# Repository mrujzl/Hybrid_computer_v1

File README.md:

# Hybrid_computer_v1
Hybrid computer for study of nonlinear dynamic systems. It was developed at Department of Radio Electronics, Brno University of Technology within the grant Development of analog computer with hybrid analog-digital components for accurate modeling of chaotic systems. This grant is realised within the project Quality Internal Grants of BUT (KInG BUT), Reg. No. CZ.02.2.69 / 0.0 / 0.0 / 19_073 / 0016948, which is financed from the OP RDE.

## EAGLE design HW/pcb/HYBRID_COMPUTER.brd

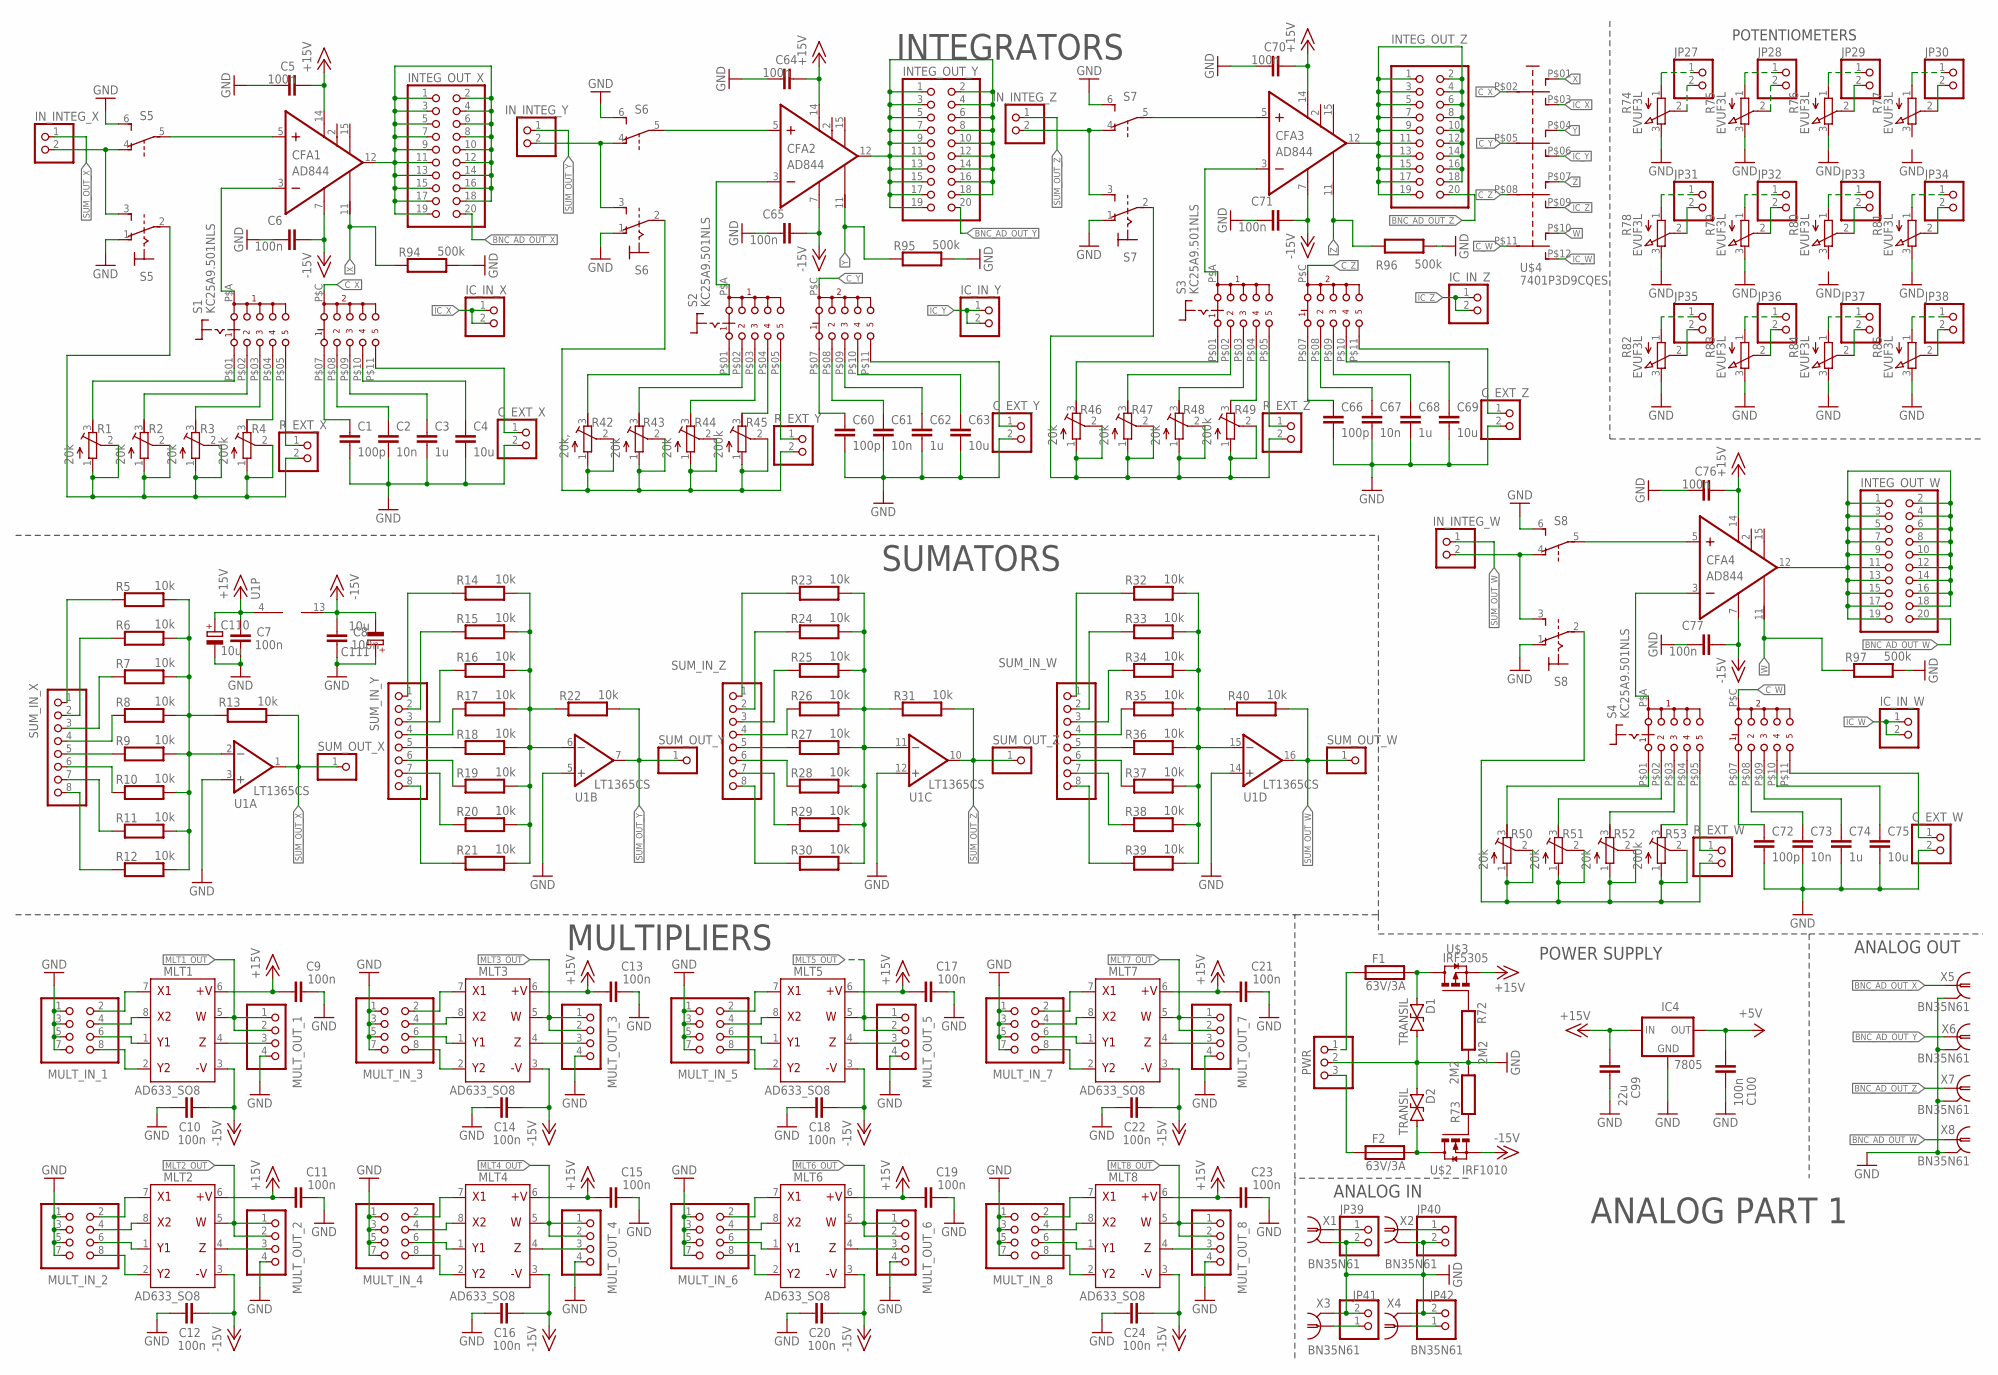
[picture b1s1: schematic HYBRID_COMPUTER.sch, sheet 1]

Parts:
C1, C60, C66, C72: 100p; C_1206
C2, C61, C67, C73: 10n; C_1206
C3, C62, C68, C74: 1u; C_1206
C4, C63, C69, C75: 10u; C_1206
C5, C6, C7, C8, C9, C10, C11, C12, C13, C14, C15, C16, C17, C18, C19, C20, C21, C22, C23, C24, C64, C65, C70, C71, C76, C77, C100: 100n; C_1206
C99: 22u; C_1206
C110, C111: 10u; E2,5-5
CFA1, CFA2, CFA3, CFA4: AD844; SOIC16R
C_EXT_W: PINHD-1X2; 1X02
C_EXT_X: PINHD-1X2; 1X02
C_EXT_Y: PINHD-1X2; 1X02
C_EXT_Z: PINHD-1X2; 1X02
D1, D2: TRANSIL; DO15-12
F1, F2: 63V/3A; FUSE_1206
IC4: 7805; 78MXXS
IC_IN_W: PINHD-1X2; 1X02
IC_IN_X: PINHD-1X2; 1X02
IC_IN_Y: PINHD-1X2; 1X02
IC_IN_Z: PINHD-1X2; 1X02
INTEG_OUT_W: PINHD-2X10; 2X10
INTEG_OUT_X: PINHD-2X10; 2X10
INTEG_OUT_Y: PINHD-2X10; 2X10
INTEG_OUT_Z: PINHD-2X10; 2X10
IN_INTEG_W: PINHD-1X2; 1X02
IN_INTEG_X: PINHD-1X2; 1X02
IN_INTEG_Y: PINHD-1X2; 1X02
IN_INTEG_Z: PINHD-1X2; 1X02
JP27, JP28, JP29, JP30, JP31, JP32, JP33, JP34, JP35, JP36, JP37, JP38, JP39, JP40, JP41, JP42: PINHD-1X2; 1X02
MLT1, MLT2, MLT3, MLT4, MLT5, MLT6, MLT7, MLT8: AD633_SO8; SO8
MULT_IN_1, MULT_IN_2, MULT_IN_3, MULT_IN_4, MULT_IN_5, MULT_IN_6, MULT_IN_7, MULT_IN_8: PINHD-2X4; 2X04
MULT_OUT_1, MULT_OUT_2, MULT_OUT_3, MULT_OUT_4, MULT_OUT_5, MULT_OUT_6, MULT_OUT_7, MULT_OUT_8: PINHD-1X4; 1X04
PWR: PINHD-1X3; 1X03
R1, R2, R3, R43, R44, R46, R47, R48, R50, R51, R52: 20k; RTRIM64W
R4, R45, R49, R53: 200k; RTRIM64W
R5, R6, R7, R8, R9, R10, R11, R12, R13, R14, R15, R16, R17, R18, R19, R20, R21, R22, R23, R24, R25, R26, R27, R28, R29, R30, R31, R32, R33, R34, R35, R36, R37, R38, R39, R40: 10k; R_1206
R42: 20k,; RTRIM64W
R72, R73: 2M2; R_1206
R74, R75, R76, R77, R78, R79, R80, R81, R82, R83, R84, R85: EVUF3L; EVUFXL
R94, R95, R96, R97: 500k; R_1206
R_EXT_W: PINHD-1X2; 1X02
R_EXT_X: PINHD-1X2; 1X02
R_EXT_Y: PINHD-1X2; 1X02
R_EXT_Z: PINHD-1X2; 1X02
S1, S2, S3, S4: KC25A9.501NLS
S5, S6, S7, S8: 320-938
SUM_IN_W: PINHD-1X8; 1X08
SUM_IN_X: PINHD-1X8; 1X08
SUM_IN_Y: PINHD-1X8; 1X08
SUM_IN_Z: PINHD-1X8; 1X08
SUM_OUT_W: PINHD-1X1; 1X01
SUM_OUT_X: PINHD-1X1; 1X01
SUM_OUT_Y: PINHD-1X1; 1X01
SUM_OUT_Z: PINHD-1X1; 1X01
U1: LT1365CS; SO16
U$2: IRF1010; TO220BV
U$3: IRF5305; TO220BV
U$4: 7401P3D9CQES
X1, X2, X3, X4, X5, X6, X7, X8: BN35N61; B35N61

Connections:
+5V: C100.1, IC4.OUT; also elsewhere on the board
+15V: C5.1, C7.1, C9.1, C11.1, C13.1, C15.1, C17.1, C19.1, C21.1, C23.1, C64.1, C70.1, C76.1, C99.1, C110.+, CFA1.14 (7), CFA2.14 (7), CFA3.14 (7), CFA4.14 (7), IC4.IN, MLT1.6 (8), MLT2.6 (8), MLT3.6 (8), MLT4.6 (8), MLT5.6 (8), MLT6.6 (8), MLT7.6 (8), MLT8.6 (8), U1.4 (V+), U$3.S; also elsewhere on the board
-15V: C6.1, C8.1, C10.1, C12.1, C14.1, C16.1, C18.1, C20.1, C22.1, C24.1, C65.1, C71.1, C77.1, C111.-, CFA1.7 (4), CFA2.7 (4), CFA3.7 (4), CFA4.7 (4), MLT1.3 (5), MLT2.3 (5), MLT3.3 (5), MLT4.3 (5), MLT5.3 (5), MLT6.3 (5), MLT7.3 (5), MLT8.3 (5), U1.13 (V-), U$2.S; also elsewhere on the board
BNC_AD_OUT_W: INTEG_OUT_W.20, X8.1; also elsewhere on the board
BNC_AD_OUT_X: INTEG_OUT_X.20, X5.1; also elsewhere on the board
BNC_AD_OUT_Y: INTEG_OUT_Y.20, X6.1; also elsewhere on the board
BNC_AD_OUT_Z: INTEG_OUT_Z.20, X7.1; also elsewhere on the board
C_W: S4.P$C (C), U$4.P$11 (11)
C_X: S1.P$C (C), U$4.P$02 (2)
C_Y: S2.P$C (C), U$4.P$05 (5)
C_Z: S3.P$C (C), U$4.P$08 (8)
GND: C1.2, C2.2, C3.2, C4.2, C5.2, C6.2, C7.2, C8.2, C9.2, C10.2, C11.2, C12.2, C13.2, C14.2, C15.2, C16.2, C17.2, C18.2, C19.2, C20.2, C21.2, C22.2, C23.2, C24.2, C60.2, C61.2, C62.2, C63.2, C64.2, C65.2, C66.2, C67.2, C68.2, C69.2, C70.2, C71.2, C72.2, C73.2, C74.2, C75.2, C76.2, C77.2, C99.2, C100.2, C110.-, C111.+, C_EXT_W.2, C_EXT_X.2, C_EXT_Y.2, C_EXT_Z.2, D1.C, D2.A, IC4.GND, JP39.2, JP40.2, JP41.2, JP42.2, MULT_IN_1.1, MULT_IN_1.3, MULT_IN_1.5, MULT_IN_1.7, MULT_IN_2.1, MULT_IN_2.3, MULT_IN_2.5, MULT_IN_2.7, MULT_IN_3.1, MULT_IN_3.3, MULT_IN_3.5, MULT_IN_3.7, MULT_IN_4.1, MULT_IN_4.3, MULT_IN_4.5, MULT_IN_4.7, MULT_IN_5.1, MULT_IN_5.3, MULT_IN_5.5, MULT_IN_5.7, MULT_IN_6.1, MULT_IN_6.3, MULT_IN_6.5, MULT_IN_6.7, MULT_IN_7.1, MULT_IN_7.3, MULT_IN_7.5, MULT_IN_7.7, MULT_IN_8.1, MULT_IN_8.3, MULT_IN_8.5, MULT_IN_8.7, MULT_OUT_1.4, MULT_OUT_2.4, MULT_OUT_3.4, MULT_OUT_4.4, MULT_OUT_5.4, MULT_OUT_6.4, MULT_OUT_7.4, MULT_OUT_8.4, PWR.2, R72.2, R73.2, R74.3 (E), R75.3 (E), R76.3 (E), R78.3 (E), R79.3 (E), R81.3 (E), R82.3 (E), R83.3 (E), R84.3 (E), R85.3 (E), R94.2, R95.2, R96.2, R97.2, S5.1 (O), S5.6 (S), S6.1 (O), S6.6 (S), S7.1 (O), S7.6 (S), S8.1 (O), S8.6 (S), U1.3 (+IN), U1.5 (+IN), U1.12 (+IN), U1.14 (+IN), X1.2, X1.3 (2), X1.4 (2), X1.5 (2), X2.2, X2.3 (2), X2.4 (2), X2.5 (2), X3.2, X3.3 (2), X3.4 (2), X3.5 (2), X4.2, X4.3 (2), X4.4 (2), X4.5 (2), X5.2, X5.3 (2), X5.4 (2), X5.5 (2), X6.2, X6.3 (2), X6.4 (2), X6.5 (2), X7.2, X7.3 (2), X7.4 (2), X7.5 (2), X8.2, X8.3 (2), X8.4 (2), X8.5 (2); also elsewhere on the board
IC_W: IC_IN_W.1, IC_IN_W.2, U$4.P$12 (12)
IC_X: IC_IN_X.1, IC_IN_X.2, U$4.P$03 (3)
IC_Y: IC_IN_Y.1, IC_IN_Y.2, U$4.P$06 (6)
IC_Z: IC_IN_Z.1, IC_IN_Z.2, U$4.P$09 (9)
INTEG_OUT_W: CFA4.12 (6), INTEG_OUT_W.1, INTEG_OUT_W.2, INTEG_OUT_W.3, INTEG_OUT_W.4, INTEG_OUT_W.5, INTEG_OUT_W.6, INTEG_OUT_W.7, INTEG_OUT_W.8, INTEG_OUT_W.9, INTEG_OUT_W.10, INTEG_OUT_W.11, INTEG_OUT_W.12, INTEG_OUT_W.13, INTEG_OUT_W.14, INTEG_OUT_W.15, INTEG_OUT_W.16, INTEG_OUT_W.17, INTEG_OUT_W.18, INTEG_OUT_W.19
INTEG_OUT_Y: CFA2.12 (6), INTEG_OUT_Y.1, INTEG_OUT_Y.2, INTEG_OUT_Y.3, INTEG_OUT_Y.4, INTEG_OUT_Y.5, INTEG_OUT_Y.6, INTEG_OUT_Y.7, INTEG_OUT_Y.8, INTEG_OUT_Y.9, INTEG_OUT_Y.10, INTEG_OUT_Y.11, INTEG_OUT_Y.12, INTEG_OUT_Y.13, INTEG_OUT_Y.14, INTEG_OUT_Y.15, INTEG_OUT_Y.16, INTEG_OUT_Y.17, INTEG_OUT_Y.18, INTEG_OUT_Y.19
INTEG_OUT_Z: CFA3.12 (6), INTEG_OUT_Z.1, INTEG_OUT_Z.2, INTEG_OUT_Z.3, INTEG_OUT_Z.4, INTEG_OUT_Z.5, INTEG_OUT_Z.6, INTEG_OUT_Z.7, INTEG_OUT_Z.8, INTEG_OUT_Z.9, INTEG_OUT_Z.10, INTEG_OUT_Z.11, INTEG_OUT_Z.12, INTEG_OUT_Z.13, INTEG_OUT_Z.14, INTEG_OUT_Z.15, INTEG_OUT_Z.16, INTEG_OUT_Z.17, INTEG_OUT_Z.18, INTEG_OUT_Z.19
MLT1_OUT: MLT1.5 (7), MULT_OUT_1.1, MULT_OUT_1.2
MLT2_OUT: MLT2.5 (7), MULT_OUT_2.1, MULT_OUT_2.2
MLT3_OUT: MLT3.5 (7), MULT_OUT_3.1, MULT_OUT_3.2
MLT4_OUT: MLT4.5 (7), MULT_OUT_4.1, MULT_OUT_4.2
MLT5_OUT: MLT5.5 (7), MULT_OUT_5.1, MULT_OUT_5.2
MLT6_OUT: MLT6.5 (7), MULT_OUT_6.1, MULT_OUT_6.2
MLT7_OUT: MLT7.5 (7), MULT_OUT_7.1, MULT_OUT_7.2
MLT8_OUT: MLT8.5 (7), MULT_OUT_8.1, MULT_OUT_8.2
unnamed: R1.1 (A), R1.2 (S), R2.1 (A), R2.2 (S), R3.1 (A), R3.2 (S), R4.1 (A), R4.2 (S), R_EXT_X.2, S5.2
unnamed: CFA1.5 (3), S5.5
unnamed: CFA1.3 (2), S1.P$A (A)
unnamed: IN_INTEG_X.2, S5.3 (S), S5.4 (O)
unnamed: R4.3 (E), S1.P$04 (4)
unnamed: R1.3 (E), S1.P$01 (1)
unnamed: R2.3 (E), S1.P$02 (2)
unnamed: R3.3 (E), S1.P$03 (3)
unnamed: C1.1, S1.P$07 (7)
unnamed: R5.2, R6.2, R7.2, R8.2, R9.2, R10.2, R11.2, R12.2, R13.1, U1.2 (-IN)
unnamed: C4.1, S1.P$10 (10)
unnamed: C3.1, S1.P$09 (9)
unnamed: C2.1, S1.P$08 (8)
unnamed: R_EXT_X.1, S1.P$05 (5)
unnamed: R9.1, SUM_IN_X.5
unnamed: C_EXT_X.1, S1.P$11 (11)
unnamed: R10.1, SUM_IN_X.6
unnamed: R11.1, SUM_IN_X.7
unnamed: R12.1, SUM_IN_X.8
unnamed: R8.1, SUM_IN_X.4
unnamed: R7.1, SUM_IN_X.3
unnamed: R6.1, SUM_IN_X.2
unnamed: R5.1, SUM_IN_X.1
unnamed: R14.2, R15.2, R16.2, R17.2, R18.2, R19.2, R20.2, R21.2, R22.1, U1.6 (-IN)
unnamed: JP29.2, R76.2 (S)
unnamed: R18.1, SUM_IN_Y.5
unnamed: R19.1, SUM_IN_Y.6
unnamed: R20.1, SUM_IN_Y.7
unnamed: R21.1, SUM_IN_Y.8
unnamed: R17.1, SUM_IN_Y.4
unnamed: R16.1, SUM_IN_Y.3
unnamed: R15.1, SUM_IN_Y.2
unnamed: R14.1, SUM_IN_Y.1
unnamed: R23.2, R24.2, R25.2, R26.2, R27.2, R28.2, R29.2, R30.2, R31.1, U1.11 (-IN)
unnamed: MLT1.7 (1), MULT_IN_1.2
unnamed: R27.1, SUM_IN_Z.5
unnamed: R28.1, SUM_IN_Z.6
unnamed: R29.1, SUM_IN_Z.7
unnamed: R30.1, SUM_IN_Z.8
unnamed: R26.1, SUM_IN_Z.4
unnamed: R25.1, SUM_IN_Z.3
unnamed: R24.1, SUM_IN_Z.2
unnamed: R23.1, SUM_IN_Z.1
unnamed: R32.2, R33.2, R34.2, R35.2, R36.2, R37.2, R38.2, R39.2, R40.1, U1.15 (-IN)
unnamed: R36.1, SUM_IN_W.5
unnamed: R37.1, SUM_IN_W.6
unnamed: R38.1, SUM_IN_W.7
unnamed: R39.1, SUM_IN_W.8
unnamed: R35.1, SUM_IN_W.4
unnamed: R34.1, SUM_IN_W.3
unnamed: R33.1, SUM_IN_W.2
unnamed: R32.1, SUM_IN_W.1
unnamed: MLT1.4 (6), MULT_OUT_1.3
unnamed: MLT1.8 (2), MULT_IN_1.4
unnamed: MLT1.1 (3), MULT_IN_1.6
unnamed: MLT1.2 (4), MULT_IN_1.8
unnamed: MLT2.4 (6), MULT_OUT_2.3
unnamed: MLT2.7 (1), MULT_IN_2.2
unnamed: MLT2.8 (2), MULT_IN_2.4
unnamed: MLT2.1 (3), MULT_IN_2.6
unnamed: MLT2.2 (4), MULT_IN_2.8
unnamed: MLT3.4 (6), MULT_OUT_3.3
unnamed: MLT3.7 (1), MULT_IN_3.2
unnamed: MLT3.8 (2), MULT_IN_3.4
unnamed: MLT3.1 (3), MULT_IN_3.6
unnamed: MLT3.2 (4), MULT_IN_3.8
unnamed: R46.1 (A), R46.2 (S), R47.1 (A), R47.2 (S), R48.1 (A), R48.2 (S), R49.1 (A), R49.2 (S), R_EXT_Z.2, S7.2
unnamed: MLT4.4 (6), MULT_OUT_4.3
unnamed: MLT4.7 (1), MULT_IN_4.2
unnamed: MLT4.8 (2), MULT_IN_4.4
unnamed: MLT4.1 (3), MULT_IN_4.6
unnamed: MLT4.2 (4), MULT_IN_4.8
unnamed: MLT5.4 (6), MULT_OUT_5.3
unnamed: MLT5.7 (1), MULT_IN_5.2
unnamed: MLT5.8 (2), MULT_IN_5.4
unnamed: MLT5.1 (3), MULT_IN_5.6
unnamed: MLT5.2 (4), MULT_IN_5.8
unnamed: MLT6.4 (6), MULT_OUT_6.3
unnamed: MLT6.7 (1), MULT_IN_6.2
unnamed: MLT6.8 (2), MULT_IN_6.4
unnamed: MLT6.1 (3), MULT_IN_6.6
unnamed: MLT6.2 (4), MULT_IN_6.8
unnamed: MLT7.4 (6), MULT_OUT_7.3
unnamed: MLT7.7 (1), MULT_IN_7.2
unnamed: MLT7.8 (2), MULT_IN_7.4
unnamed: MLT7.1 (3), MULT_IN_7.6
unnamed: MLT7.2 (4), MULT_IN_7.8
unnamed: MLT8.4 (6), MULT_OUT_8.3
unnamed: MLT8.7 (1), MULT_IN_8.2
unnamed: MLT8.8 (2), MULT_IN_8.4
unnamed: MLT8.1 (3), MULT_IN_8.6
unnamed: MLT8.2 (4), MULT_IN_8.8
unnamed: JP27.1, R74.1 (A)
unnamed: JP27.2, R74.2 (S)
unnamed: JP28.2, R75.2 (S)
unnamed: JP28.1, R75.1 (A)
unnamed: JP29.1, R76.1 (A)
unnamed: JP30.1, R77.1 (A)
unnamed: JP30.2, R77.2 (S)
unnamed: JP34.1, R81.1 (A)
unnamed: JP34.2, R81.2 (S)
unnamed: JP33.2, R80.2 (S)
unnamed: JP33.1, R80.1 (A)
unnamed: JP32.1, R79.1 (A)
unnamed: JP32.2, R79.2 (S)
unnamed: JP31.1, R78.1 (A)
unnamed: JP31.2, R78.2 (S)
unnamed: JP35.1, R82.1 (A)
unnamed: JP35.2, R82.2 (S)
unnamed: JP36.1, R83.1 (A)
unnamed: JP36.2, R83.2 (S)
unnamed: JP37.1, R84.1 (A)
unnamed: JP37.2, R84.2 (S)
unnamed: JP38.1, R85.1 (A)
unnamed: JP38.2, R85.2 (S)
unnamed: D1.A, F1.2, U$3.D
unnamed: R42.1 (A), R42.2 (S), R43.1 (A), R43.2 (S), R44.1 (A), R44.2 (S), R45.1 (A), R45.2 (S), R_EXT_Y.2, S6.2
unnamed: CFA2.5 (3), S6.5
unnamed: CFA2.3 (2), S2.P$A (A)
unnamed: IN_INTEG_Y.2, S6.3 (S), S6.4 (O)
unnamed: R42.3 (E), S2.P$01 (1)
unnamed: R43.3 (E), S2.P$02 (2)
unnamed: R44.3 (E), S2.P$03 (3)
unnamed: C63.1, S2.P$10 (10)
unnamed: C62.1, S2.P$09 (9)
unnamed: C61.1, S2.P$08 (8)
unnamed: CFA1.12 (6), INTEG_OUT_X.1, INTEG_OUT_X.2, INTEG_OUT_X.3, INTEG_OUT_X.4, INTEG_OUT_X.5, INTEG_OUT_X.6, INTEG_OUT_X.7, INTEG_OUT_X.8, INTEG_OUT_X.9, INTEG_OUT_X.10, INTEG_OUT_X.11, INTEG_OUT_X.12, INTEG_OUT_X.13, INTEG_OUT_X.14, INTEG_OUT_X.15, INTEG_OUT_X.16, INTEG_OUT_X.17, INTEG_OUT_X.18, INTEG_OUT_X.19
unnamed: R45.3 (E), S2.P$04 (4)
unnamed: C60.1, S2.P$07 (7)
unnamed: R_EXT_Y.1, S2.P$05 (5)
unnamed: C_EXT_Y.1, S2.P$11 (11)
unnamed: CFA3.5 (3), S7.5
unnamed: CFA3.3 (2), S3.P$A (A)
unnamed: IN_INTEG_Z.2, S7.3 (S), S7.4 (O)
unnamed: R46.3 (E), S3.P$01 (1)
unnamed: R47.3 (E), S3.P$02 (2)
unnamed: R48.3 (E), S3.P$03 (3)
unnamed: C69.1, S3.P$10 (10)
unnamed: C68.1, S3.P$09 (9)
unnamed: C67.1, S3.P$08 (8)
unnamed: R49.3 (E), S3.P$04 (4)
unnamed: C66.1, S3.P$07 (7)
unnamed: R_EXT_Z.1, S3.P$05 (5)
unnamed: C_EXT_Z.1, S3.P$11 (11)
unnamed: R50.1 (A), R50.2 (S), R51.1 (A), R51.2 (S), R52.1 (A), R52.2 (S), R53.1 (A), R53.2 (S), R_EXT_W.2, S8.2
unnamed: CFA4.5 (3), S8.5
unnamed: CFA4.3 (2), S4.P$A (A)
unnamed: IN_INTEG_W.2, S8.3 (S), S8.4 (O)
unnamed: R50.3 (E), S4.P$01 (1)
unnamed: R51.3 (E), S4.P$02 (2)
unnamed: R52.3 (E), S4.P$03 (3)
unnamed: C75.1, S4.P$10 (10)
unnamed: C74.1, S4.P$09 (9)
unnamed: C73.1, S4.P$08 (8)
unnamed: R53.3 (E), S4.P$04 (4)
unnamed: C72.1, S4.P$07 (7)
unnamed: R_EXT_W.1, S4.P$05 (5)
unnamed: C_EXT_W.1, S4.P$11 (11)
unnamed: F2.1, PWR.3
unnamed: F1.1, PWR.1
unnamed: JP39.1, X1.1
unnamed: JP40.1, X2.1
unnamed: JP41.1, X3.1
unnamed: JP42.1, X4.1
unnamed: D2.C, F2.2, U$2.D
unnamed: R72.1, U$3.G
unnamed: R73.1, U$2.G
SUM_OUT_W: IN_INTEG_W.1, R40.2, SUM_OUT_W.1, U1.16 (OUT)
SUM_OUT_X: IN_INTEG_X.1, R13.2, SUM_OUT_X.1, U1.1 (OUT)
SUM_OUT_Y: IN_INTEG_Y.1, R22.2, SUM_OUT_Y.1, U1.7 (OUT)
SUM_OUT_Z: IN_INTEG_Z.1, R31.2, SUM_OUT_Z.1, U1.10 (OUT)
W: CFA4.11 (5), R97.1, U$4.P$10 (10)
X: CFA1.11 (5), R94.1, U$4.P$01 (1)
Y: CFA2.11 (5), R95.1, U$4.P$04 (4)
Z: CFA3.11 (5), R96.1, U$4.P$07 (7)

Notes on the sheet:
ANALOG PART 1
INTEGRATORS
ANALOG OUT
SUMATORS
POWER SUPPLY
MULTIPLIERS
POTENTIOMETERS
ANALOG IN

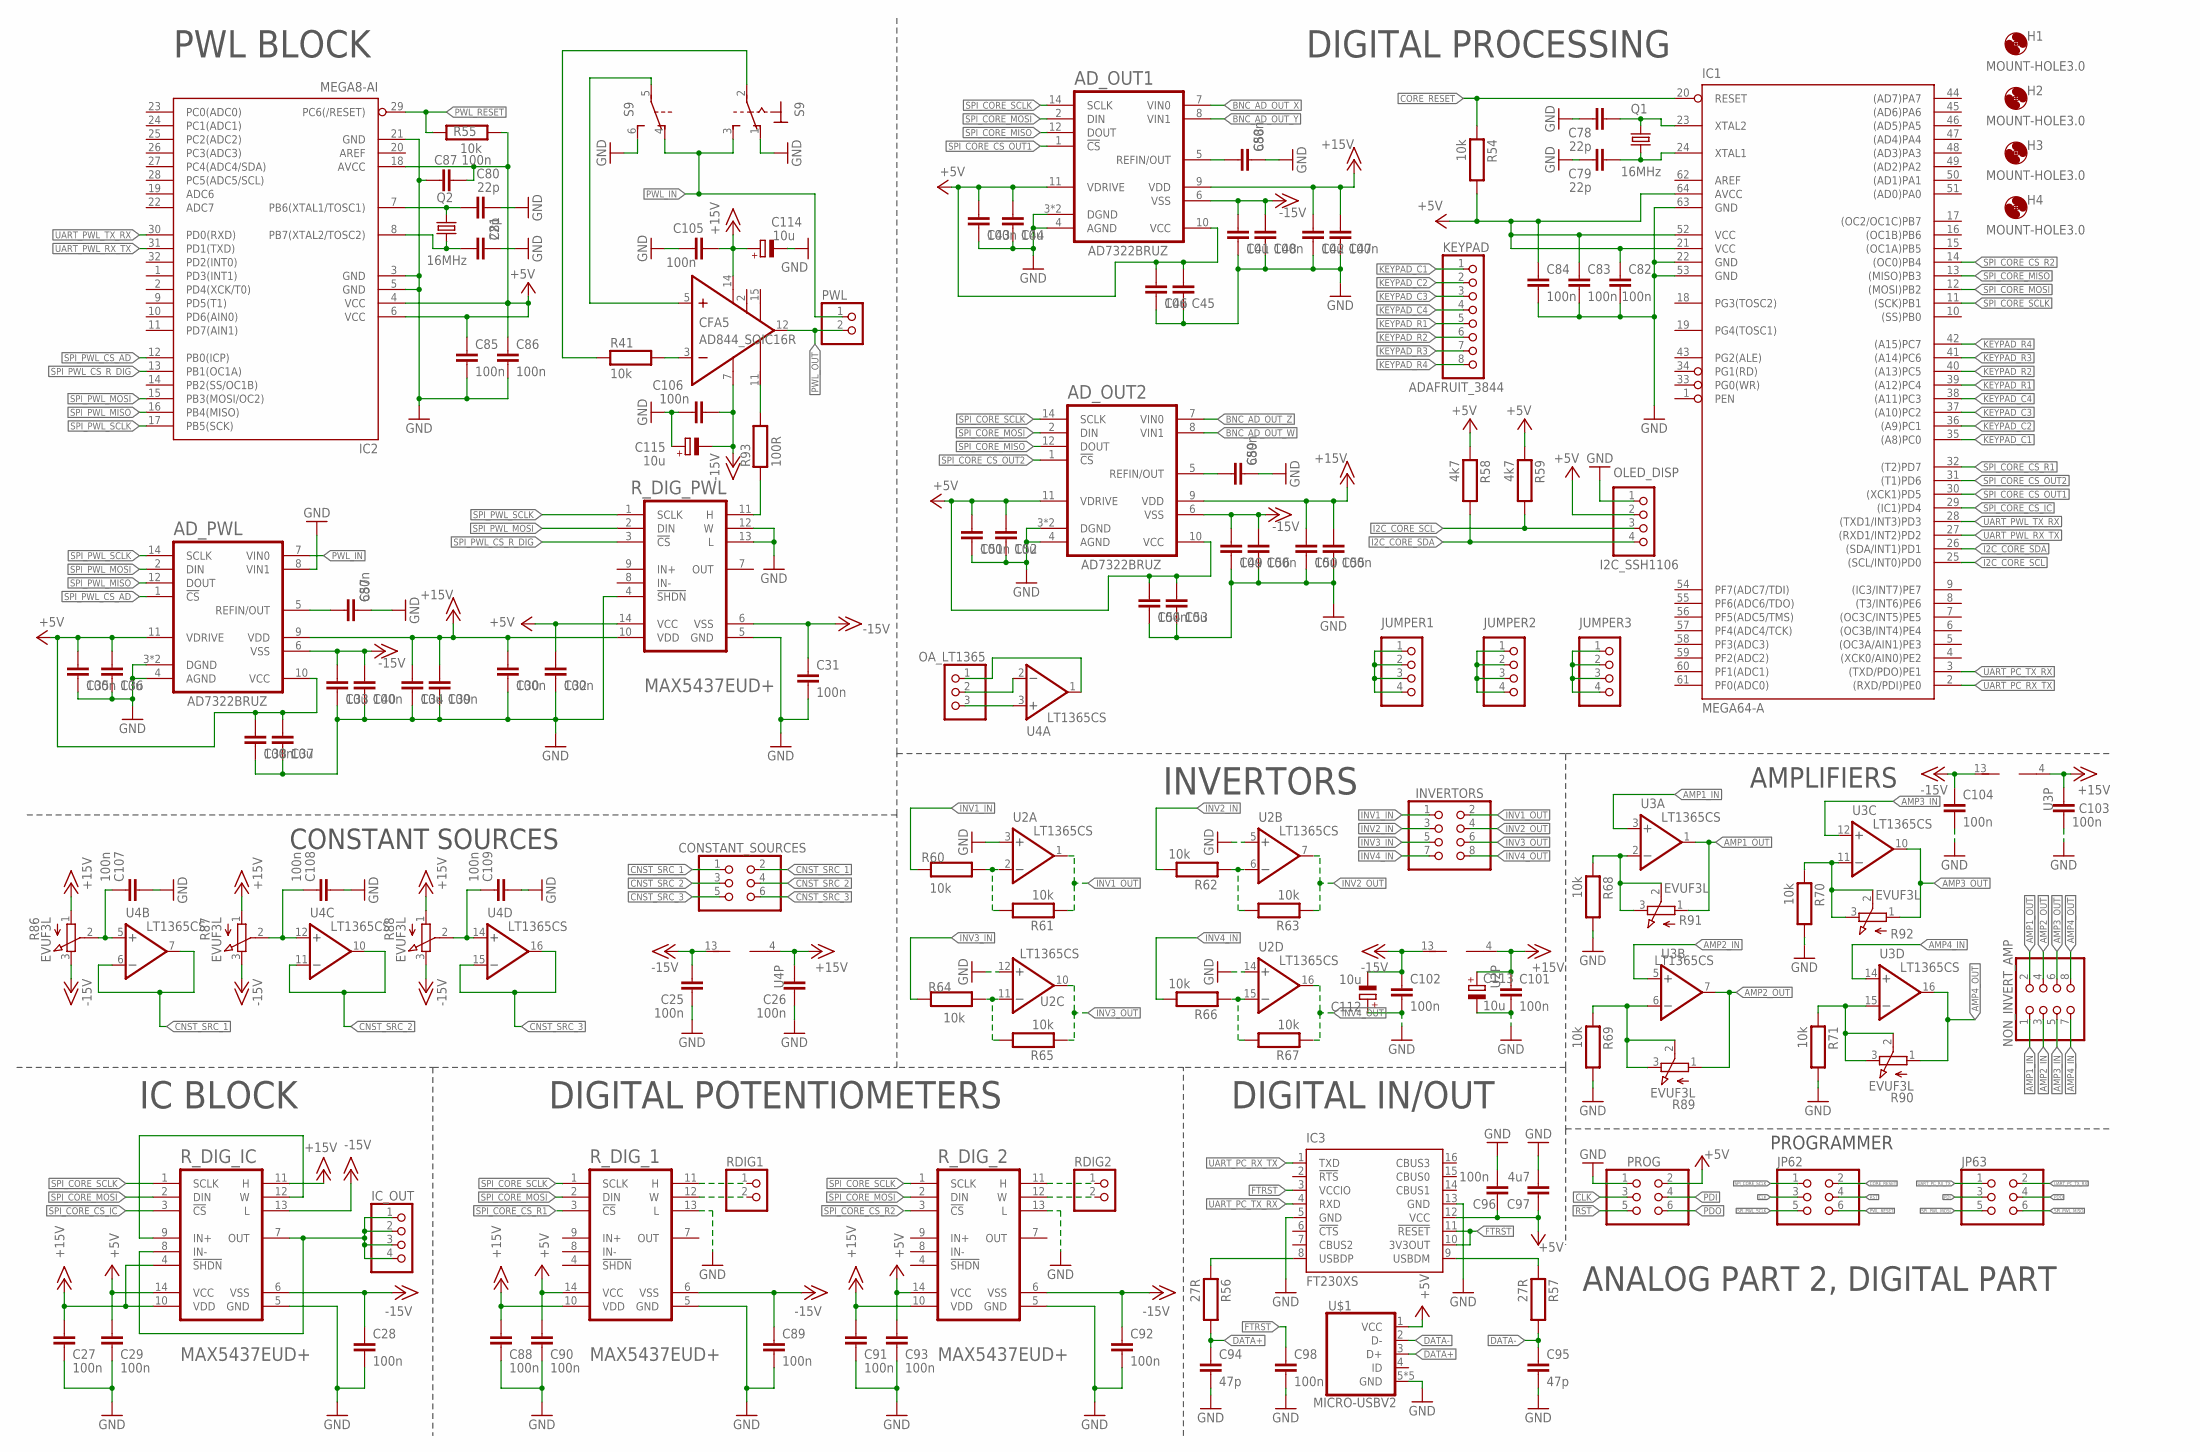
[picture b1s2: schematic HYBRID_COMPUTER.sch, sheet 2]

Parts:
AD_OUT1, AD_OUT2: AD7322; TSSOP-14
AD_PWL: AD7322; TSSOP-14
C25, C26, C27, C28, C29, C30, C31, C32, C35, C38, C39, C40, C43, C47, C48, C51, C54, C55, C56, C82, C83, C84, C85, C86, C87, C88, C89, C90, C91, C92, C93, C96, C98, C101, C102, C103, C104, C105, C106, C107, C108, C109: 100n; C_1206
C33, C34, C36, C37, C41, C42, C44, C46, C49, C50, C52, C53: 10u; C_1206
C45: C_1206
C57, C58, C59: 680n; C_1206
C78, C79, C80, C81: 22p; C_1206
C94, C95: 47p; C_1206
C97: 4u7; C_1206
C112, C113, C114, C115: 10u; E2,5-5
CFA5: AD844_SOIC16R; SOIC16R
CONSTANT_SOURCES: PINHD-2X3; 2X03
H1, H2, H3, H4: MOUNT-HOLE3.0; 3,0
IC1: MEGA64-A; TQFP64
IC2: MEGA8-AI; TQFP32-08
IC3: FT230XS; SSOP16
IC_OUT: PINHD-1X4; 1X04
INVERTORS: PINHD-2X4; 2X04
JP62, JP63: PINHD-2X3; 2X03
JUMPER1, JUMPER2, JUMPER3: PINHD-1X4; 1X04
KEYPAD: ADAFRUIT_3844; 1X08
NON_INVERT_AMP: PINHD-2X4; 2X04
OA_LT1365: PINHD-1X3; 1X03
OLED_DISP: I2C_SSH1106; 1X04
PROG: PINHD-2X3; 2X03
PWL: PINHD-1X2; 1X02
Q1, Q2: 16MHz; HC49/S
R41, R54, R55, R60, R61, R62, R63, R64, R65, R66, R67, R68, R69, R70, R71: 10k; R_1206
R56, R57: 27R; R_1206
R58, R59: 4k7; R_1206
R86, R87, R88, R89, R90, R91, R92: EVUF3L; EVUFXL
R93: 100R; R_1206
RDIG1, RDIG2: PINHD-1X2; 1X02
R_DIG_1, R_DIG_2: MAXIM_MAX5437EUD+MAXIM_MAX5437EUD+_0_0; MAXIM_MAX5437EUD+_0
R_DIG_IC: MAXIM_MAX5437EUD+MAXIM_MAX5437EUD+_0_0; MAXIM_MAX5437EUD+_0
R_DIG_PWL: MAXIM_MAX5437EUD+MAXIM_MAX5437EUD+_0_0; MAXIM_MAX5437EUD+_0
S9: 320-938
U2, U3, U4: LT1365CS; SO16
U$1: MICRO-USBV2; MICRO-USB-2

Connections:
+5V: AD_OUT1.10 (VCC), AD_OUT1.11 (VDRIVE), AD_OUT2.10 (VCC), AD_OUT2.11 (VDRIVE), AD_PWL.10 (VCC), AD_PWL.11 (VDRIVE), C29.1, C32.1, C35.1, C36.1, C37.1, C38.1, C43.1, C44.1, C45.1, C46.1, C51.1, C52.1, C53.1, C54.1, C82.1, C83.1, C84.1, C85.1, C86.1, C87.1, C90.1, C93.1, C96.1, C97.1, IC1.21 (VCC), IC1.52 (VCC), IC1.64 (AVCC), IC2.4 (VCC), IC2.6 (VCC), IC2.18 (AVCC), IC3.12 (VCC), OLED_DISP.2, PROG.2, R54.2, R55.2, R58.1, R59.1, R_DIG_1.14 (VCC), R_DIG_2.14 (VCC), R_DIG_IC.14 (VCC), R_DIG_PWL.14 (VCC), U$1.1 (VCC); also elsewhere on the board
+15V: AD_OUT1.9 (VDD), AD_OUT2.9 (VDD), AD_PWL.9 (VDD), C26.2, C27.1, C30.1, C34.1, C39.1, C42.1, C47.1, C50.1, C55.1, C88.1, C91.1, C101.1, C103.1, C105.1, C113.+, C114.+, CFA5.14 (7), R86.1 (A), R87.1 (A), R88.1 (A), R_DIG_1.10 (VDD), R_DIG_2.10 (VDD), R_DIG_IC.4 (!SHDN!), R_DIG_IC.10 (VDD), R_DIG_IC.11 (H), R_DIG_PWL.10 (VDD), U2.4 (V+), U3.4 (V+), U4.4 (V+); also elsewhere on the board
-15V: AD_OUT1.6 (VSS), AD_OUT2.6 (VSS), AD_PWL.6 (VSS), C25.2, C28.1, C31.1, C33.1, C40.1, C41.1, C48.1, C49.1, C56.1, C89.1, C92.1, C102.1, C104.1, C106.1, C112.-, C115.-, CFA5.7 (4), R86.3 (E), R87.3 (E), R88.3 (E), R_DIG_1.6 (VSS), R_DIG_2.6 (VSS), R_DIG_IC.6 (VSS), R_DIG_IC.13 (L), R_DIG_PWL.6 (VSS), U2.13 (V-), U3.13 (V-), U4.13 (V-); also elsewhere on the board
AMP1_IN: NON_INVERT_AMP.1, U3.3 (+IN)
AMP1_OUT: NON_INVERT_AMP.2, R91.1 (A), U3.1 (OUT)
AMP2_IN: NON_INVERT_AMP.3, U3.5 (+IN)
AMP2_OUT: NON_INVERT_AMP.4, R89.1 (A), U3.7 (OUT)
AMP3_IN: NON_INVERT_AMP.5, U3.12 (+IN)
AMP3_OUT: NON_INVERT_AMP.6, R92.1 (A), U3.10 (OUT)
AMP4_IN: NON_INVERT_AMP.7, U3.14 (+IN)
AMP4_OUT: NON_INVERT_AMP.8, R90.1 (A), U3.16 (OUT)
BNC_AD_OUT_W: AD_OUT2.8 (VIN1); also elsewhere on the board
BNC_AD_OUT_X: AD_OUT1.7 (VIN0); also elsewhere on the board
BNC_AD_OUT_Y: AD_OUT1.8 (VIN1); also elsewhere on the board
BNC_AD_OUT_Z: AD_OUT2.7 (VIN0); also elsewhere on the board
CLK: JP62.3, PROG.3
CNST_SRC_1: CONSTANT_SOURCES.1, CONSTANT_SOURCES.2, U4.6 (-IN), U4.7 (OUT)
CNST_SRC_2: CONSTANT_SOURCES.3, CONSTANT_SOURCES.4, U4.10 (OUT), U4.11 (-IN)
CNST_SRC_3: CONSTANT_SOURCES.5, CONSTANT_SOURCES.6, U4.15 (-IN), U4.16 (OUT)
CORE_RESET: IC1.20 (RESET), JP62.2, R54.1
DATA+: C94.1, R56.2, U$1.3 (D+)
DATA-: C95.1, R57.2, U$1.2 (D-)
FTRST: C98.1, IC3.3 (VCCIO), IC3.10 (3V3OUT), IC3.11 (!RESET)
GND: AD_OUT1.3 (DGND), AD_OUT1.4 (AGND), AD_OUT1.13 (DGND), AD_OUT2.3 (DGND), AD_OUT2.4 (AGND), AD_OUT2.13 (DGND), AD_PWL.3 (DGND), AD_PWL.4 (AGND), AD_PWL.8 (VIN1), AD_PWL.13 (DGND), C25.1, C26.1, C27.2, C28.2, C29.2, C30.2, C31.2, C32.2, C33.2, C34.2, C35.2, C36.2, C37.2, C38.2, C39.2, C40.2, C41.2, C42.2, C43.2, C44.2, C45.2, C46.2, C47.2, C48.2, C49.2, C50.2, C51.2, C52.2, C53.2, C54.2, C55.2, C56.2, C57.2, C58.2, C59.2, C78.1, C79.1, C80.2, C81.2, C82.2, C83.2, C84.2, C85.2, C86.2, C87.2, C88.2, C89.2, C90.2, C91.2, C92.2, C93.2, C94.2, C95.2, C96.2, C97.2, C98.2, C101.2, C102.2, C103.2, C104.2, C105.2, C106.2, C107.2, C108.2, C109.2, C112.+, C113.-, C114.-, C115.+, IC1.22 (GND), IC1.53 (GND), IC1.63 (GND), IC2.3 (GND), IC2.5 (GND), IC2.21 (GND), IC3.5 (GND), IC3.13 (GND), OLED_DISP.1, PROG.1, R68.2, R69.2, R70.2, R71.2, R_DIG_1.5 (GND), R_DIG_1.13 (L), R_DIG_2.5 (GND), R_DIG_2.13 (L), R_DIG_IC.5 (GND), R_DIG_PWL.4 (!SHDN!), R_DIG_PWL.5 (GND), R_DIG_PWL.12 (W), R_DIG_PWL.13 (L), S9.1 (O), S9.6 (S), U2.3 (+IN), U2.5 (+IN), U2.12 (+IN), U2.14 (+IN), U$1.5 (GND), U$1.P$1 (GND), U$1.P$2 (GND), U$1.P$3 (GND), U$1.P$4 (GND); also elsewhere on the board
I2C_CORE_SCL: IC1.25 ((SCL/INT0)PD0), OLED_DISP.3, R59.2
I2C_CORE_SDA: IC1.26 ((SDA/INT1)PD1), OLED_DISP.4, R58.2
INV1_IN: INVERTORS.1, R60.2
INV1_OUT: INVERTORS.2, R61.1, U2.1 (OUT)
INV2_IN: INVERTORS.3, R62.2
INV2_OUT: INVERTORS.4, R63.1, U2.7 (OUT)
INV3_IN: INVERTORS.5, R64.2
INV3_OUT: INVERTORS.6, R65.1, U2.10 (OUT)
INV4_IN: INVERTORS.7, R66.2
INV4_OUT: INVERTORS.8, R67.1, U2.16 (OUT)
KEYPAD_C1: IC1.35 ((A8)PC0), KEYPAD.1
KEYPAD_C2: IC1.36 ((A9)PC1), KEYPAD.2
KEYPAD_C3: IC1.37 ((A10)PC2), KEYPAD.3
KEYPAD_C4: IC1.38 ((A11)PC3), KEYPAD.4
KEYPAD_R1: IC1.39 ((A12)PC4), KEYPAD.5
KEYPAD_R2: IC1.40 ((A13)PC5), KEYPAD.6
KEYPAD_R3: IC1.41 ((A14)PC6), KEYPAD.7
KEYPAD_R4: IC1.42 ((A15)PC7), KEYPAD.8
unnamed: R93.1, R_DIG_PWL.11 (H)
unnamed: OA_LT1365.3, U4.3 (+IN)
unnamed: CFA5.5 (3), S9.5
unnamed: R68.1, R91.2 (S), R91.3 (E), U3.2 (-IN)
unnamed: R69.1, R89.2 (S), R89.3 (E), U3.6 (-IN)
unnamed: CFA5.3 (2), R41.2
unnamed: R41.1, S9.2
unnamed: R70.1, R92.2 (S), R92.3 (E), U3.11 (-IN)
unnamed: OA_LT1365.2, U4.2 (-IN)
unnamed: C107.1, R86.2 (S), U4.5 (+IN)
unnamed: OA_LT1365.1, U4.1 (OUT)
unnamed: R71.1, R90.2 (S), R90.3 (E), U3.15 (-IN)
unnamed: C109.1, R88.2 (S), U4.14 (+IN)
unnamed: R_DIG_IC.9 (IN+), R_DIG_IC.12 (W)
unnamed: IC_OUT.1, IC_OUT.2, IC_OUT.3, IC_OUT.4, R_DIG_IC.7 (OUT), R_DIG_IC.8 (IN-)
unnamed: C108.1, R87.2 (S), U4.12 (+IN)
unnamed: CFA5.11 (5), R93.2
unnamed: JUMPER1.1, JUMPER1.2, JUMPER1.3, JUMPER1.4
unnamed: AD_PWL.5 (REFIN/OUT), C57.1
unnamed: AD_OUT1.5 (REFIN/OUT), C58.1
unnamed: AD_OUT2.5 (REFIN/OUT), C59.1
unnamed: JUMPER2.1, JUMPER2.2, JUMPER2.3, JUMPER2.4
unnamed: JUMPER3.1, JUMPER3.2, JUMPER3.3, JUMPER3.4
unnamed: C80.1, IC2.7 (PB6(XTAL1/TOSC1)), Q2.2
unnamed: C81.1, IC2.8 (PB7(XTAL2/TOSC2)), Q2.1
unnamed: C78.2, IC1.23 (XTAL2), Q1.2
unnamed: C79.2, IC1.24 (XTAL1), Q1.1
unnamed: RDIG1.1, R_DIG_1.11 (H)
unnamed: RDIG1.2, R_DIG_1.12 (W)
unnamed: RDIG2.1, R_DIG_2.11 (H)
unnamed: RDIG2.2, R_DIG_2.12 (W)
unnamed: IC3.8 (USBDP), R56.1
unnamed: IC3.9 (USBDM), R57.1
unnamed: R60.1, R61.2, U2.2 (-IN)
unnamed: R62.1, R63.2, U2.6 (-IN)
unnamed: R66.1, R67.2, U2.15 (-IN)
unnamed: R64.1, R65.2, U2.11 (-IN)
PDI: JP63.3, PROG.4
PDO: JP63.4, PROG.6
PWL_IN: AD_PWL.7 (VIN0), PWL.1, S9.3 (S), S9.4 (O)
PWL_OUT: CFA5.12 (6), PWL.2
PWL_RESET: IC2.29 (PC6(/RESET)), JP62.6, R55.1
RST: JP62.4, PROG.5
SPI_CORE_CS_IC: IC1.29 ((IC1)PD4), R_DIG_IC.3 (!CS!)
SPI_CORE_CS_OUT1: AD_OUT1.1 (!CS!), IC1.30 ((XCK1)PD5)
SPI_CORE_CS_OUT2: AD_OUT2.1 (!CS!), IC1.31 ((T1)PD6)
SPI_CORE_CS_R1: IC1.32 ((T2)PD7), R_DIG_1.3 (!CS!)
SPI_CORE_CS_R2: IC1.14 ((OC0)PB4), R_DIG_2.3 (!CS!)
SPI_CORE_MISO: AD_OUT1.12 (DOUT), AD_OUT2.12 (DOUT), IC1.13 ((MISO)PB3)
SPI_CORE_MOSI: AD_OUT1.2 (DIN), AD_OUT2.2 (DIN), IC1.12 ((MOSI)PB2), R_DIG_1.2 (DIN), R_DIG_2.2 (DIN), R_DIG_IC.2 (DIN)
SPI_CORE_SCLK: AD_OUT1.14 (SCLK), AD_OUT2.14 (SCLK), IC1.11 ((SCK)PB1), JP62.1, R_DIG_1.1 (SCLK), R_DIG_2.1 (SCLK), R_DIG_IC.1 (SCLK)
SPI_PWL_CS_AD: AD_PWL.1 (!CS!), IC2.12 (PB0(ICP))
SPI_PWL_CS_R_DIG: IC2.13 (PB1(OC1A)), R_DIG_PWL.3 (!CS!)
SPI_PWL_MISO: AD_PWL.12 (DOUT), IC2.16 (PB4(MISO)), JP63.6
SPI_PWL_MOSI: AD_PWL.2 (DIN), IC2.15 (PB3(MOSI/OC2)), JP63.5, R_DIG_PWL.2 (DIN)
SPI_PWL_SCLK: AD_PWL.14 (SCLK), IC2.17 (PB5(SCK)), JP62.5, R_DIG_PWL.1 (SCLK)
UART_PC_RX_TX: IC1.2 ((RXD/PDI)PE0), IC3.1 (TXD), JP63.1
UART_PC_TX_RX: IC1.3 ((TXD/PDO)PE1), IC3.4 (RXD), JP63.2
UART_PWL_RX_TX: IC1.27 ((RXD1/INT2)PD2), IC2.31 (PD1(TXD))
UART_PWL_TX_RX: IC1.28 ((TXD1/INT3)PD3), IC2.30 (PD0(RXD))

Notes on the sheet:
ANALOG PART 2, DIGITAL PART
PWL BLOCK
IC BLOCK
DIGITAL PROCESSING
DIGITAL IN/OUT
CONSTANT SOURCES
PROGRAMMER
DIGITAL POTENTIOMETERS
INVERTORS
AMPLIFIERS

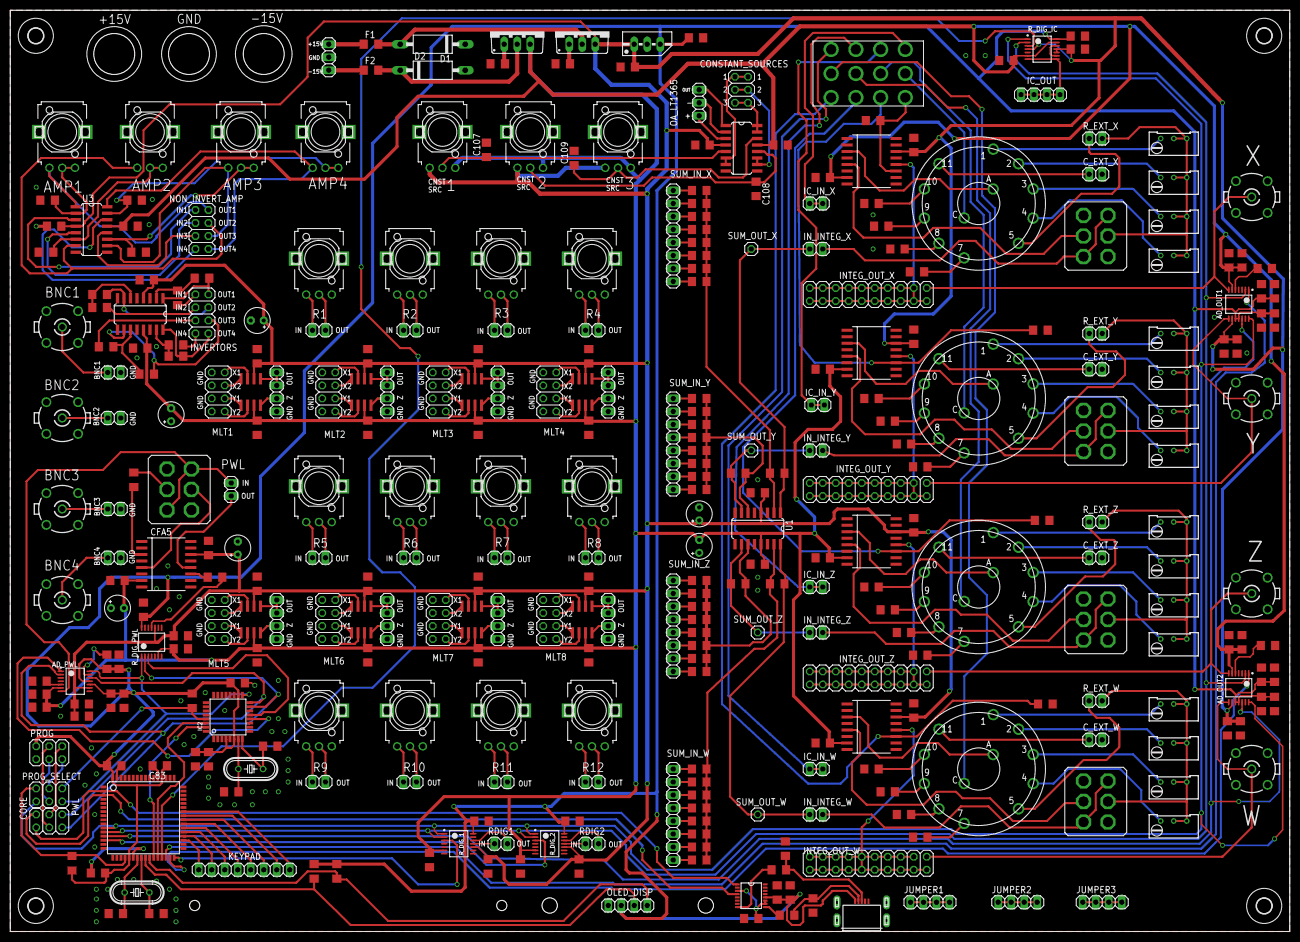
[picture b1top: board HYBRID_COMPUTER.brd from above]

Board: 2 copper layers, 250.0 x 180.0 mm, 348 parts (0 on the bottom side), 296 nets.

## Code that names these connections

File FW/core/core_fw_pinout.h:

/*
 * core_fw_pinout.h
 *
 * Created: 16.10.2022
 *  Author: Miroslav Rujzl
 */ 


#ifndef CORE_FW_PINOUT_H_
#define CORE_FW_PINOUT_H_

// PINOUT
#define UART_PC_RX_PIN        0
#define UART_PC_TX_PIN        1
#define UART_PWL_RX_PIN       20
#define UART_PWL_TX_PIN       21

#define I2C_SDA_PIN           18
#define I2C_SDA_PIN           19

#define SPI_SCLK_PIN          9
#define SPI_MOSI_PIN          10
#define SPI_MISO_PIN          11
#define SPI_CS_RDIG_IC_PIN    22
#define SPI_CS_AD_XY_PIN      23
#define SPI_CS_AD_ZW_PIN      24
#define SPI_CS_RDIG_1_PIN     25
#define SPI_CS_RDIG_2_PIN     12

#define KEYPAD_R1_PIN         32
#define KEYPAD_R2_PIN         33
#define KEYPAD_R3_PIN         34
#define KEYPAD_R4_PIN         35
#define KEYPAD_C1_PIN         28
#define KEYPAD_C2_PIN         29
#define KEYPAD_C3_PIN         30
#define KEYPAD_C4_PIN         31

#endif /* CORE_FW_PINOUT_H_ */
